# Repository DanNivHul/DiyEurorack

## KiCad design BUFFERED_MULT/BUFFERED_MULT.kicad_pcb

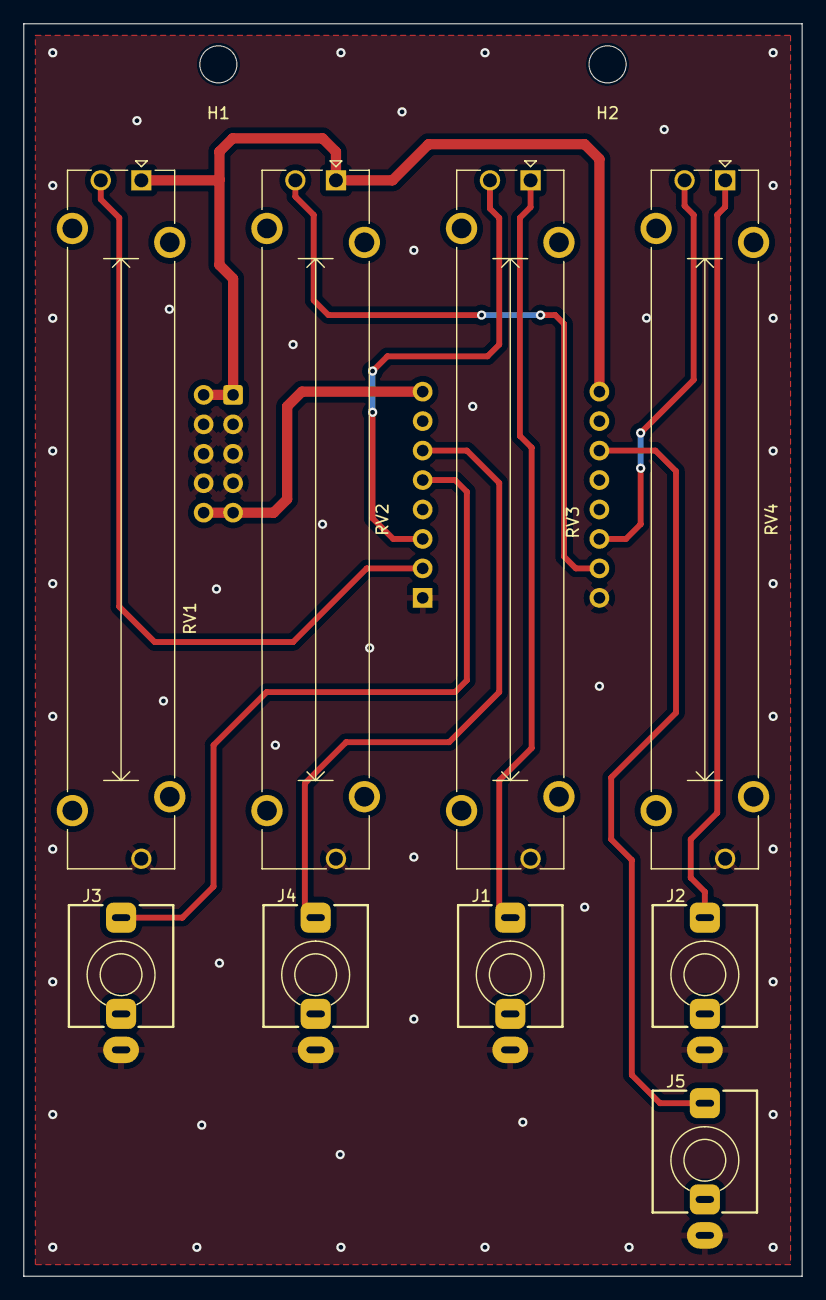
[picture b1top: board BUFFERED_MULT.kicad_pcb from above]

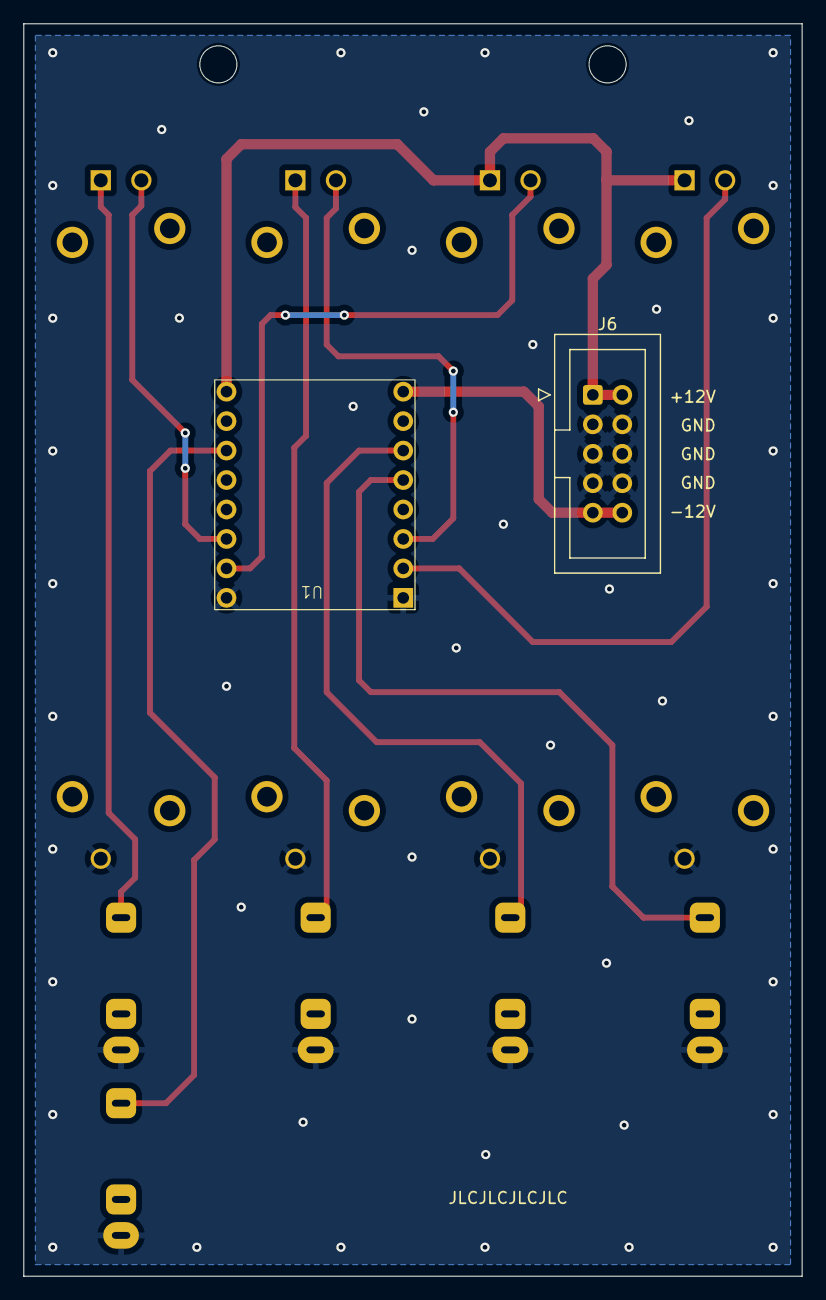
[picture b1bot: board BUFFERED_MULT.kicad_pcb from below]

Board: 2 copper layers, 67.1 x 108.0 mm, 13 parts (2 on the bottom side), 12 nets.

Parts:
H1, H2: MountingHole; MountingHole_3.2mm_M3
J1, J2, J3, J4, J5: AudioJack2; Jack_3.5mm_QingPu_WQP-PJ398SM_Vertical
J6: Conn_02x05_Odd_Even; IDC-Header_2x05_P2.54mm_Vertical
RV1, RV2, RV3, RV4: R_Potentiometer; Potentiometer_Bourns_PTA4543_Single_Slide
U1: 2144_LPF; Electrosmith_2144_LPF

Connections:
+12V: J6.1, J6.2, RV1.1, RV2.1, U1.9 (VCC)
-12V: J6.9, J6.10, U1.8 (VEE)
CUTOFF_CV: RV3.2, U1.3 (Cutoff_CV)
CUTOFF_POT: RV1.2, U1.2 (Cutoff_Pot)
GND: J1.S, J2.S, J3.S, J4.S, J5.S, J6.3, J6.4, J6.5, J6.6, J6.7, J6.8, RV1.3, RV2.3, RV3.3, RV4.3, U1.1 (GND), U1.16 (GND)
INPUT_1: J3.T, U1.5 (Input_1)
INPUT_2: J4.T, U1.6 (Input_2)
unnamed: J1.T, RV3.1
unnamed: J2.T, RV4.1
OUTPUT: J5.T, U1.11 (Output)
RESONANCE_CV: RV4.2, U1.14 (Resonance_CV)
RESONANCE_POT: RV2.2, U1.15 (Resonance_Pot)

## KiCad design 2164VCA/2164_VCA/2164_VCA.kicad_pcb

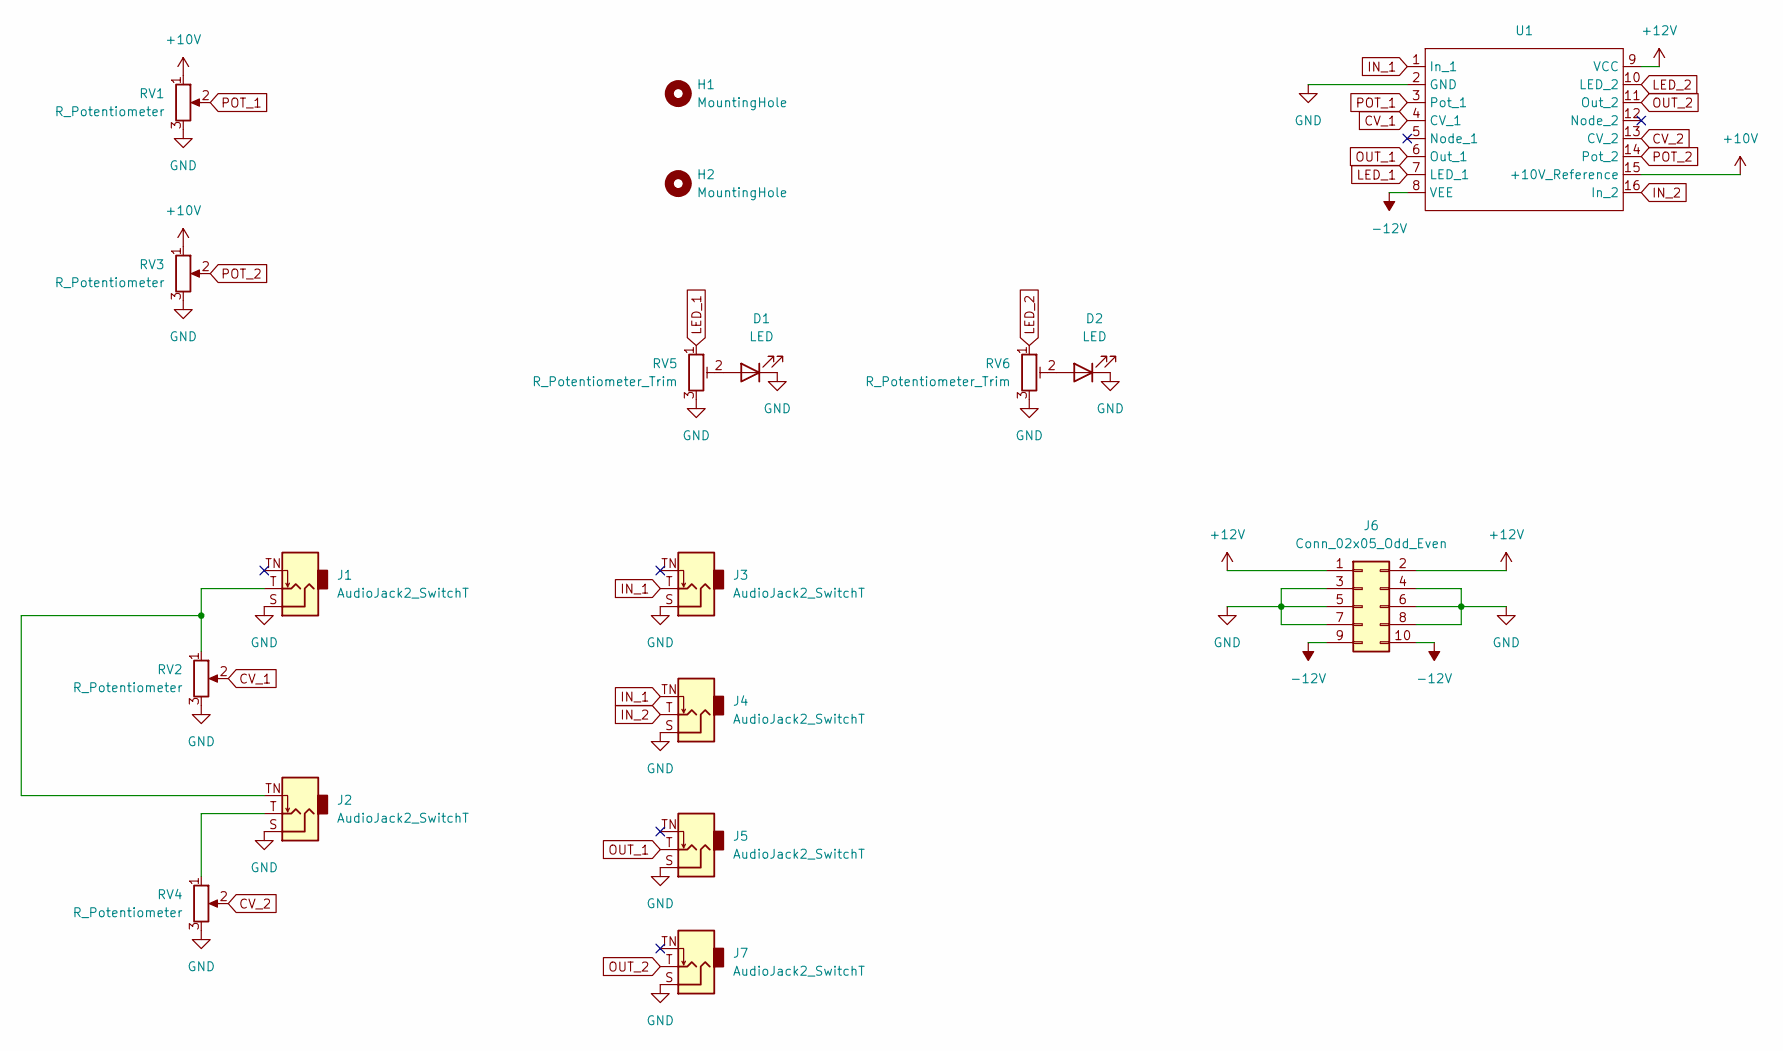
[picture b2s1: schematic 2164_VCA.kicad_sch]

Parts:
D1, D2: LED; LED_D3.0mm
H1, H2: MountingHole; MountingHole_3.2mm_M3
J1, J2, J3, J4, J5, J7: AudioJack2_SwitchT; Jack_3.5mm_QingPu_WQP-PJ398SM_Vertical
J6: Conn_02x05_Odd_Even; IDC-Header_2x05_P2.54mm_Vertical
RV1, RV2, RV3, RV4: R_Potentiometer; Potentiometer_Bourns_PTA4543_Single_Slide
RV5, RV6: R_Potentiometer_Trim; Potentiometer_Bourns_3296Y_Vertical
U1: Electrosmith_2164_VCA

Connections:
+10V: RV1.1, RV3.1, U1.15 (+10V_Reference)
+12V: J6.1, J6.2, U1.9 (VCC)
-12V: J6.9, J6.10, U1.8 (VEE)
CV_1: RV2.2, U1.4 (CV_1)
CV_2: RV4.2, U1.13 (CV_2)
GND: D1.1 (K), D2.1 (K), J1.S, J2.S, J3.S, J4.S, J5.S, J6.3, J6.4, J6.5, J6.6, J6.7, J6.8, J7.S, RV1.3, RV2.3, RV3.3, RV4.3, RV5.3, RV6.3, U1.2 (GND)
IN_1: J3.T, J4.TN, U1.1 (In_1)
IN_2: J4.T, U1.16 (In_2)
LED_1: RV5.1, U1.7 (LED_1)
LED_2: RV6.1, U1.10 (LED_2)
unnamed: D1.2 (A), RV5.2
unnamed: D2.2 (A), RV6.2
unnamed: J1.T, J2.TN, RV2.1
unnamed: J2.T, RV4.1
OUT_1: J5.T, U1.6 (Out_1)
OUT_2: J7.T, U1.11 (Out_2)
POT_1: RV1.2, U1.3 (Pot_1)
POT_2: RV3.2, U1.14 (Pot_2)

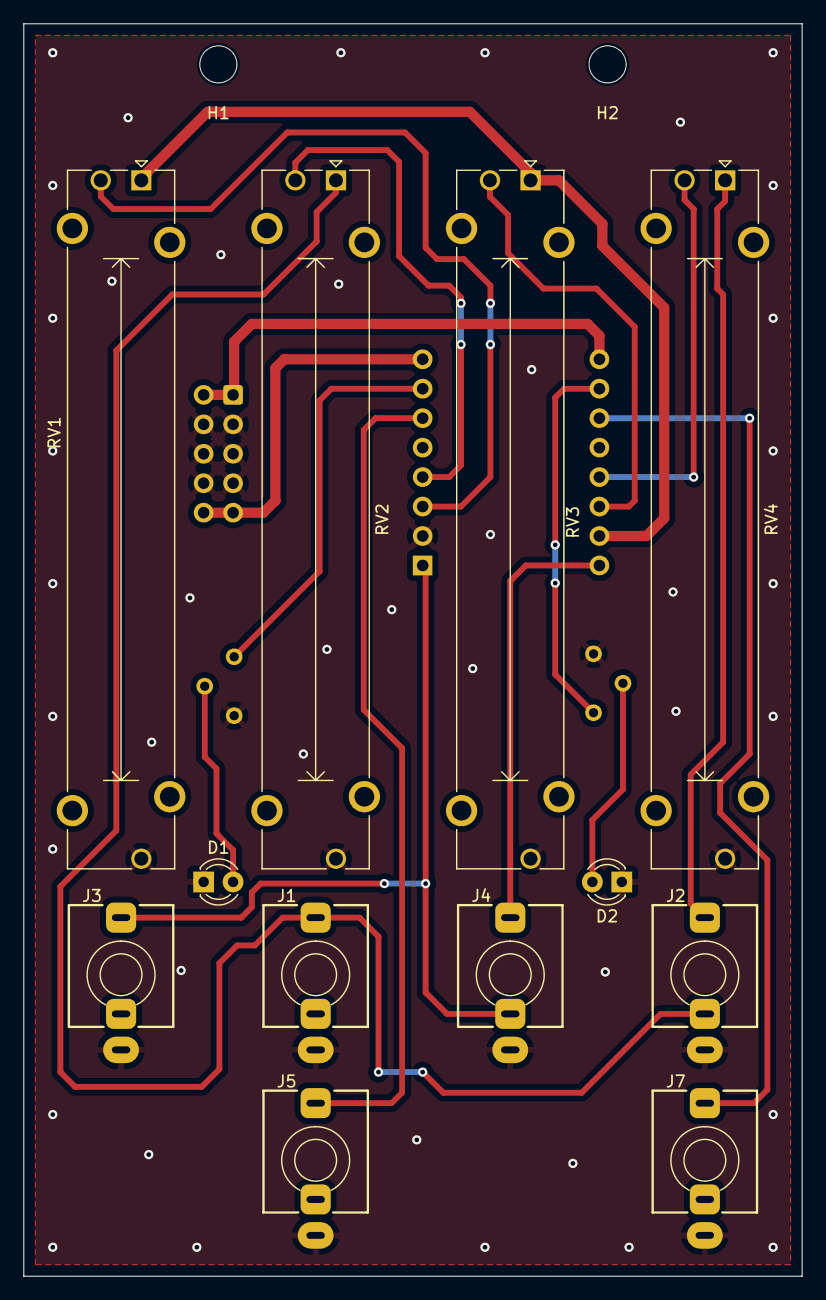
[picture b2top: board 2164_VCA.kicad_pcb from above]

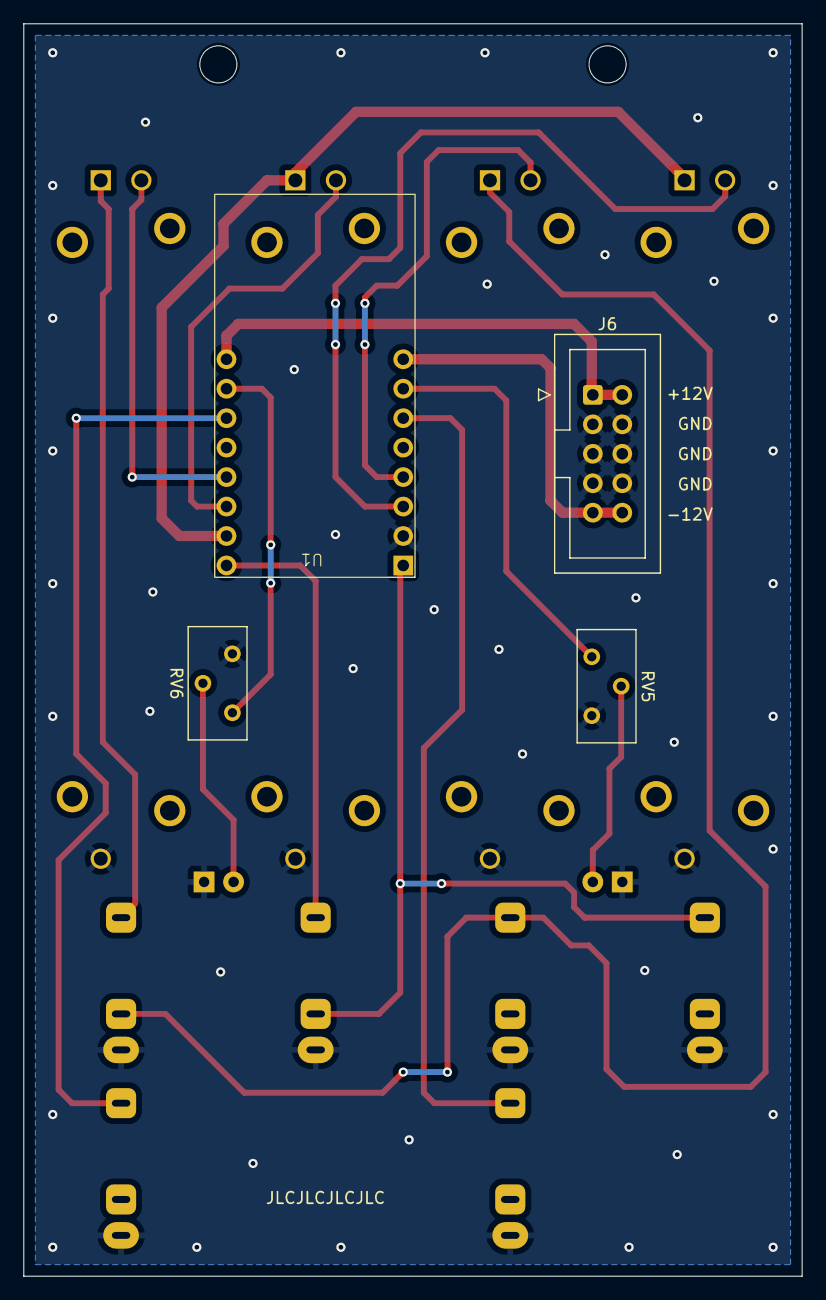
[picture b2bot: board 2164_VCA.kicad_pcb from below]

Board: 2 copper layers, 67.1 x 108.0 mm, 18 parts (4 on the bottom side), 18 nets.

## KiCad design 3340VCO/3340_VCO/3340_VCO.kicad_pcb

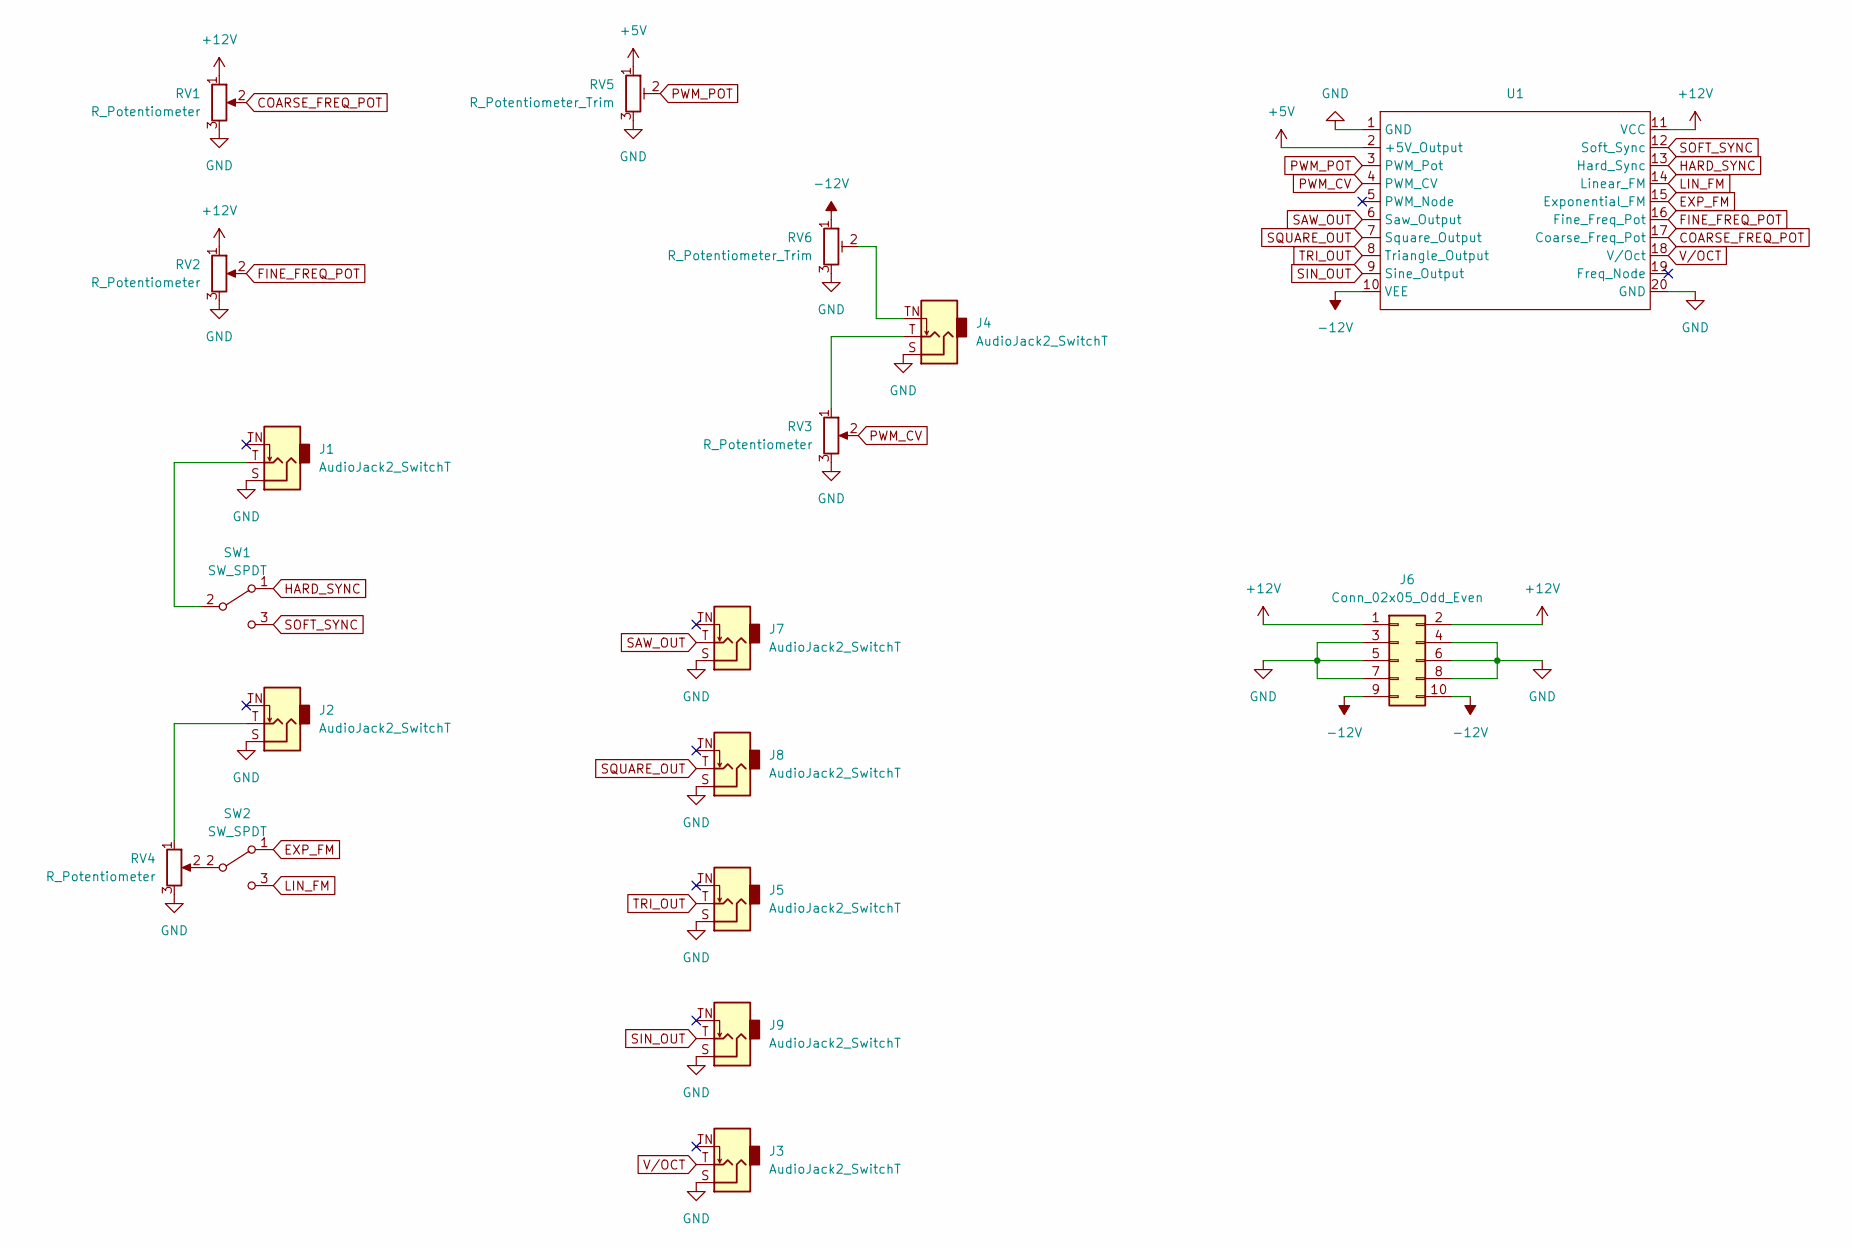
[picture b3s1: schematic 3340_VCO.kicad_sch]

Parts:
J1, J2, J3, J4, J5, J7, J8, J9: AudioJack2_SwitchT; Jack_3.5mm_QingPu_WQP-PJ398SM_Vertical
J6: Conn_02x05_Odd_Even; IDC-Header_2x05_P2.54mm_Vertical
RV1, RV2, RV3, RV4: R_Potentiometer; Potentiometer_Bourns_PTA4543_Single_Slide
RV5, RV6: R_Potentiometer_Trim; Potentiometer_Bourns_3296Y_Vertical
SW1, SW2: SW_SPDT; Salecom_SPDT_PCB_Mount_Mini_Toggle_Switch
U1: Electrosmith_3340_VCO

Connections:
+5V: RV5.1, U1.2 (+5V_Output)
+12V: J6.1, J6.2, RV1.1, RV2.1, U1.11 (VCC)
-12V: J6.9, J6.10, RV6.1, U1.10 (VEE)
COARSE_FREQ_POT: RV1.2, U1.17 (Coarse_Freq_Pot)
EXP_FM: SW2.1 (A), U1.15 (Exponential_FM)
FINE_FREQ_POT: RV2.2, U1.16 (Fine_Freq_Pot)
GND: J1.S, J2.S, J3.S, J4.S, J5.S, J6.3, J6.4, J6.5, J6.6, J6.7, J6.8, J7.S, J8.S, J9.S, RV1.3, RV2.3, RV3.3, RV4.3, RV5.3, RV6.3, U1.1 (GND), U1.20 (GND)
HARD_SYNC: SW1.1 (A), U1.13 (Hard_Sync)
LIN_FM: SW2.3 (C), U1.14 (Linear_FM)
unnamed: J2.T, RV4.1
unnamed: J4.T, RV3.1
unnamed: J4.TN, RV6.2
unnamed: J1.T, SW1.2 (B)
unnamed: RV4.2, SW2.2 (B)
PWM_CV: RV3.2, U1.4 (PWM_CV)
PWM_POT: RV5.2, U1.3 (PWM_Pot)
SAW_OUT: J7.T, U1.6 (Saw_Output)
SIN_OUT: J9.T, U1.9 (Sine_Output)
SOFT_SYNC: SW1.3 (C), U1.12 (Soft_Sync)
SQUARE_OUT: J8.T, U1.7 (Square_Output)
TRI_OUT: J5.T, U1.8 (Triangle_Output)
V/OCT: J3.T, U1.18 (V/Oct)

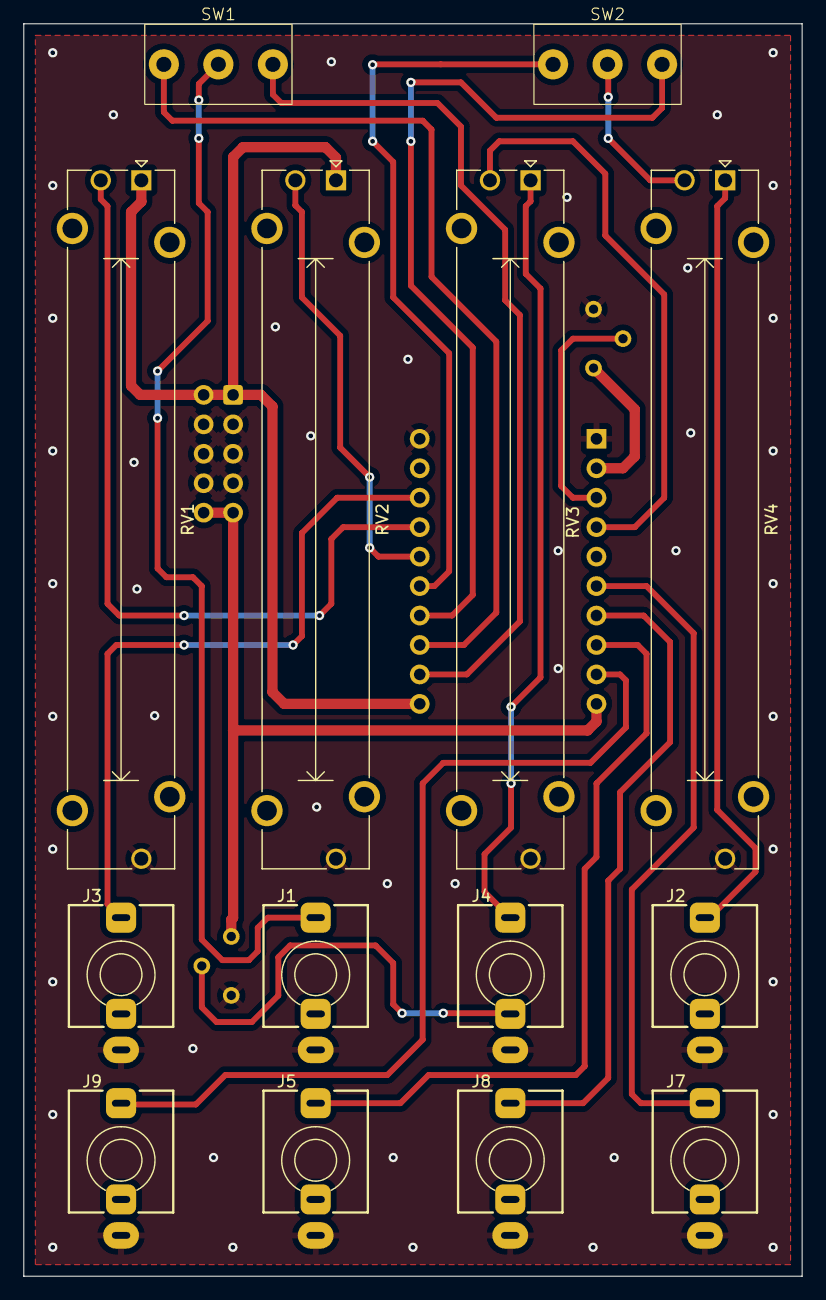
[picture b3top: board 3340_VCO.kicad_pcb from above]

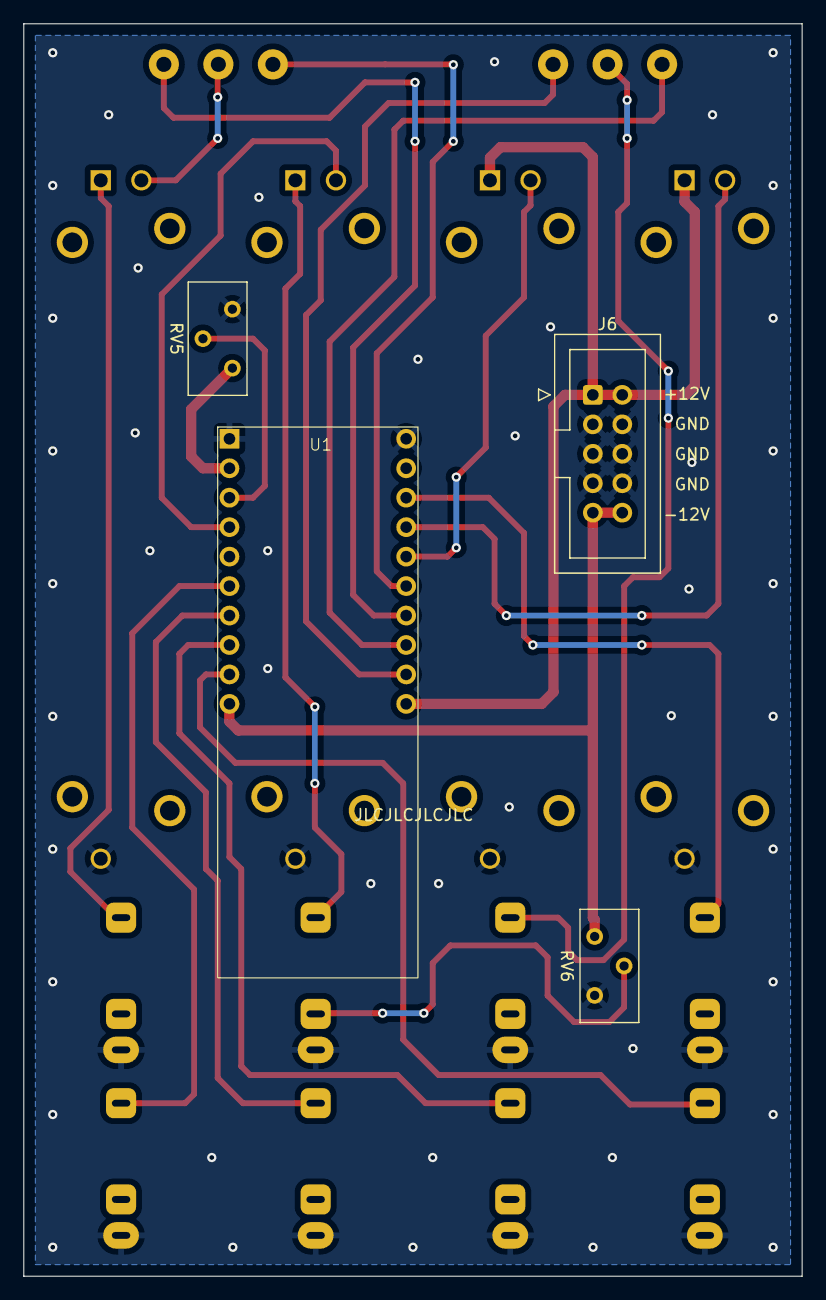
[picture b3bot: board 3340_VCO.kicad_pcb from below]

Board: 2 copper layers, 67.1 x 108.0 mm, 18 parts (4 on the bottom side), 22 nets.

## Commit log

2025-11-12 backups updated
2025-11-13 update vca panel
2025-11-14 create buffered mult project
2025-11-14 updating buffered mult schematic
